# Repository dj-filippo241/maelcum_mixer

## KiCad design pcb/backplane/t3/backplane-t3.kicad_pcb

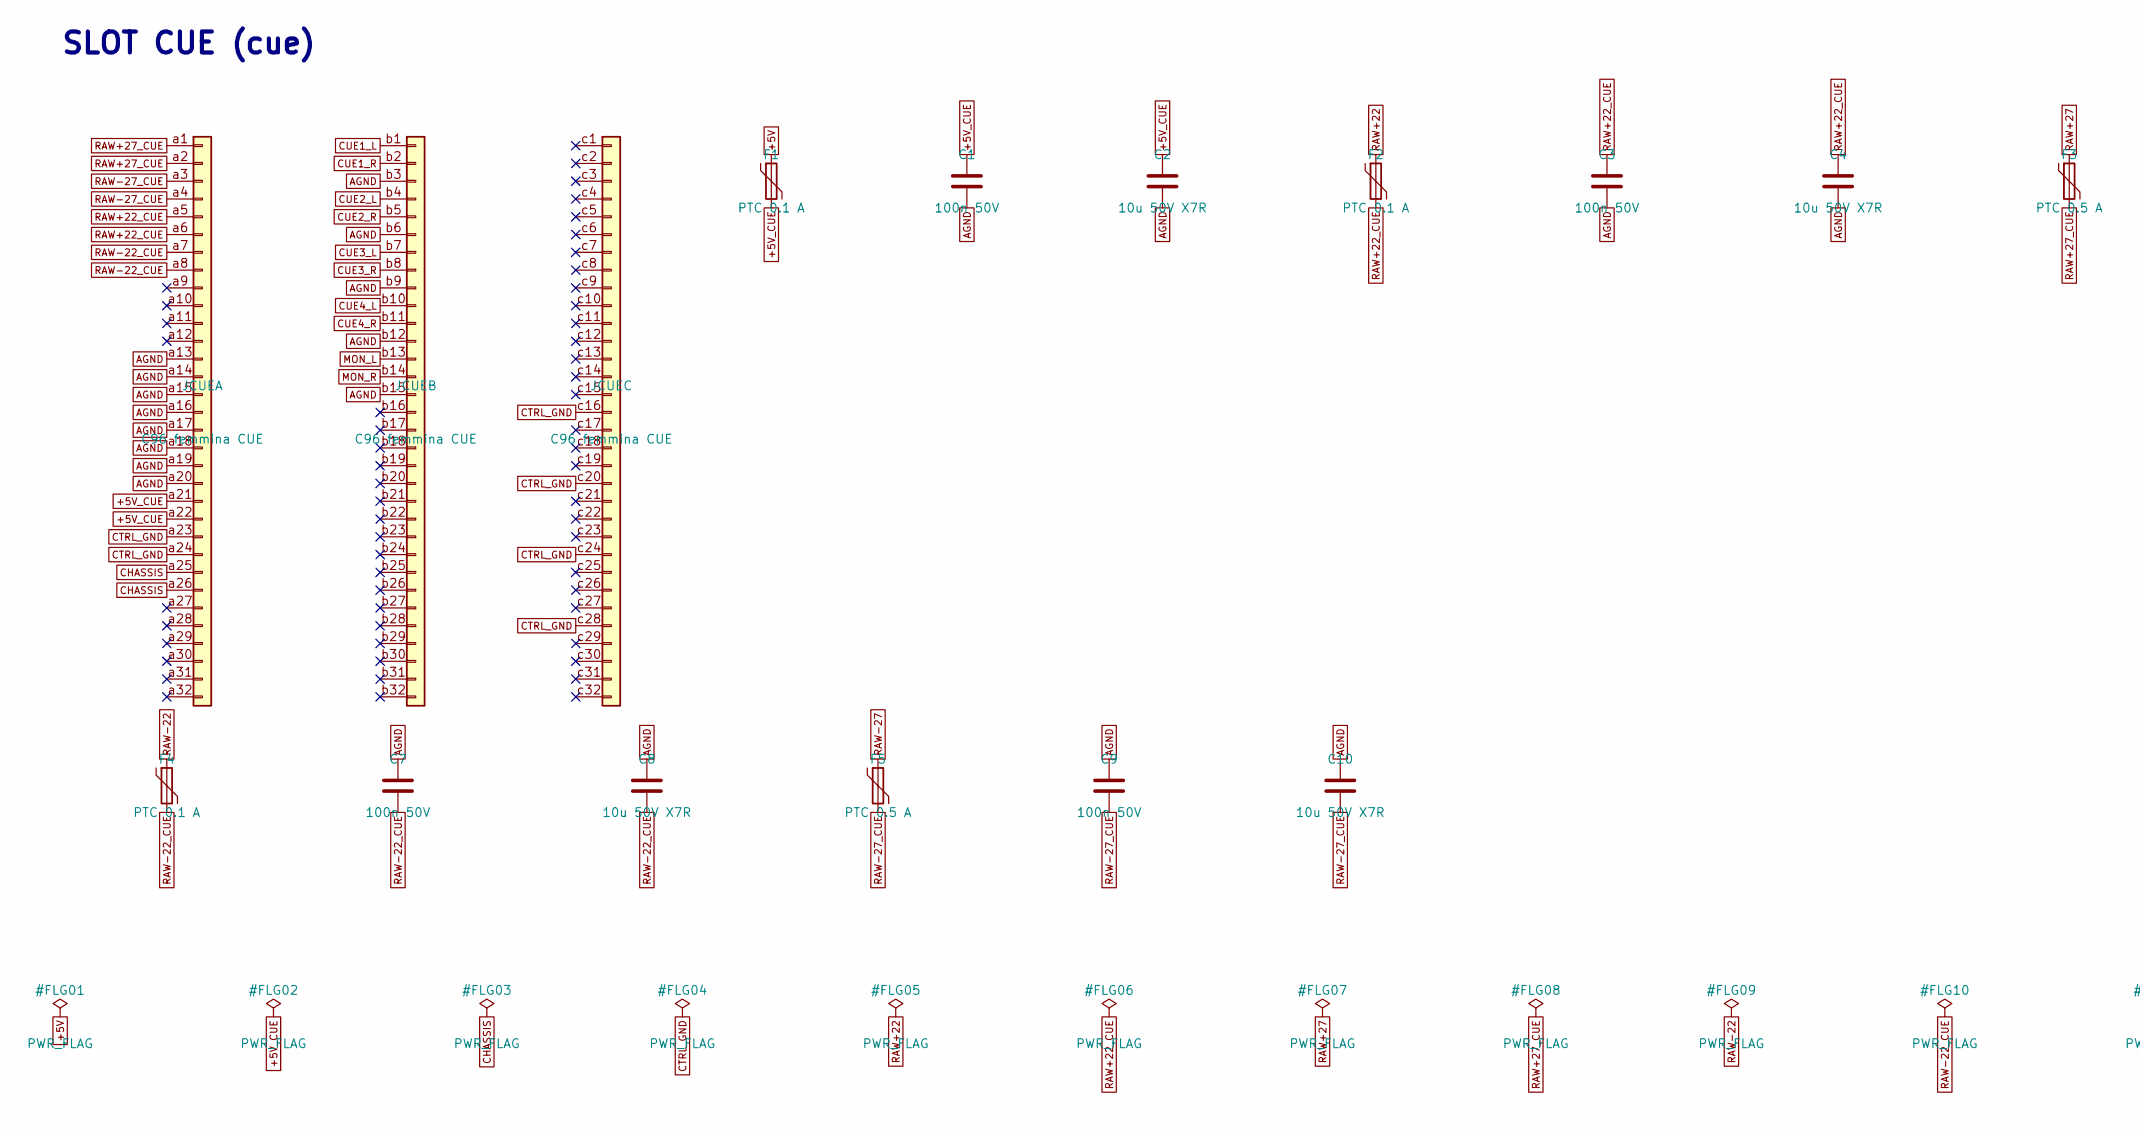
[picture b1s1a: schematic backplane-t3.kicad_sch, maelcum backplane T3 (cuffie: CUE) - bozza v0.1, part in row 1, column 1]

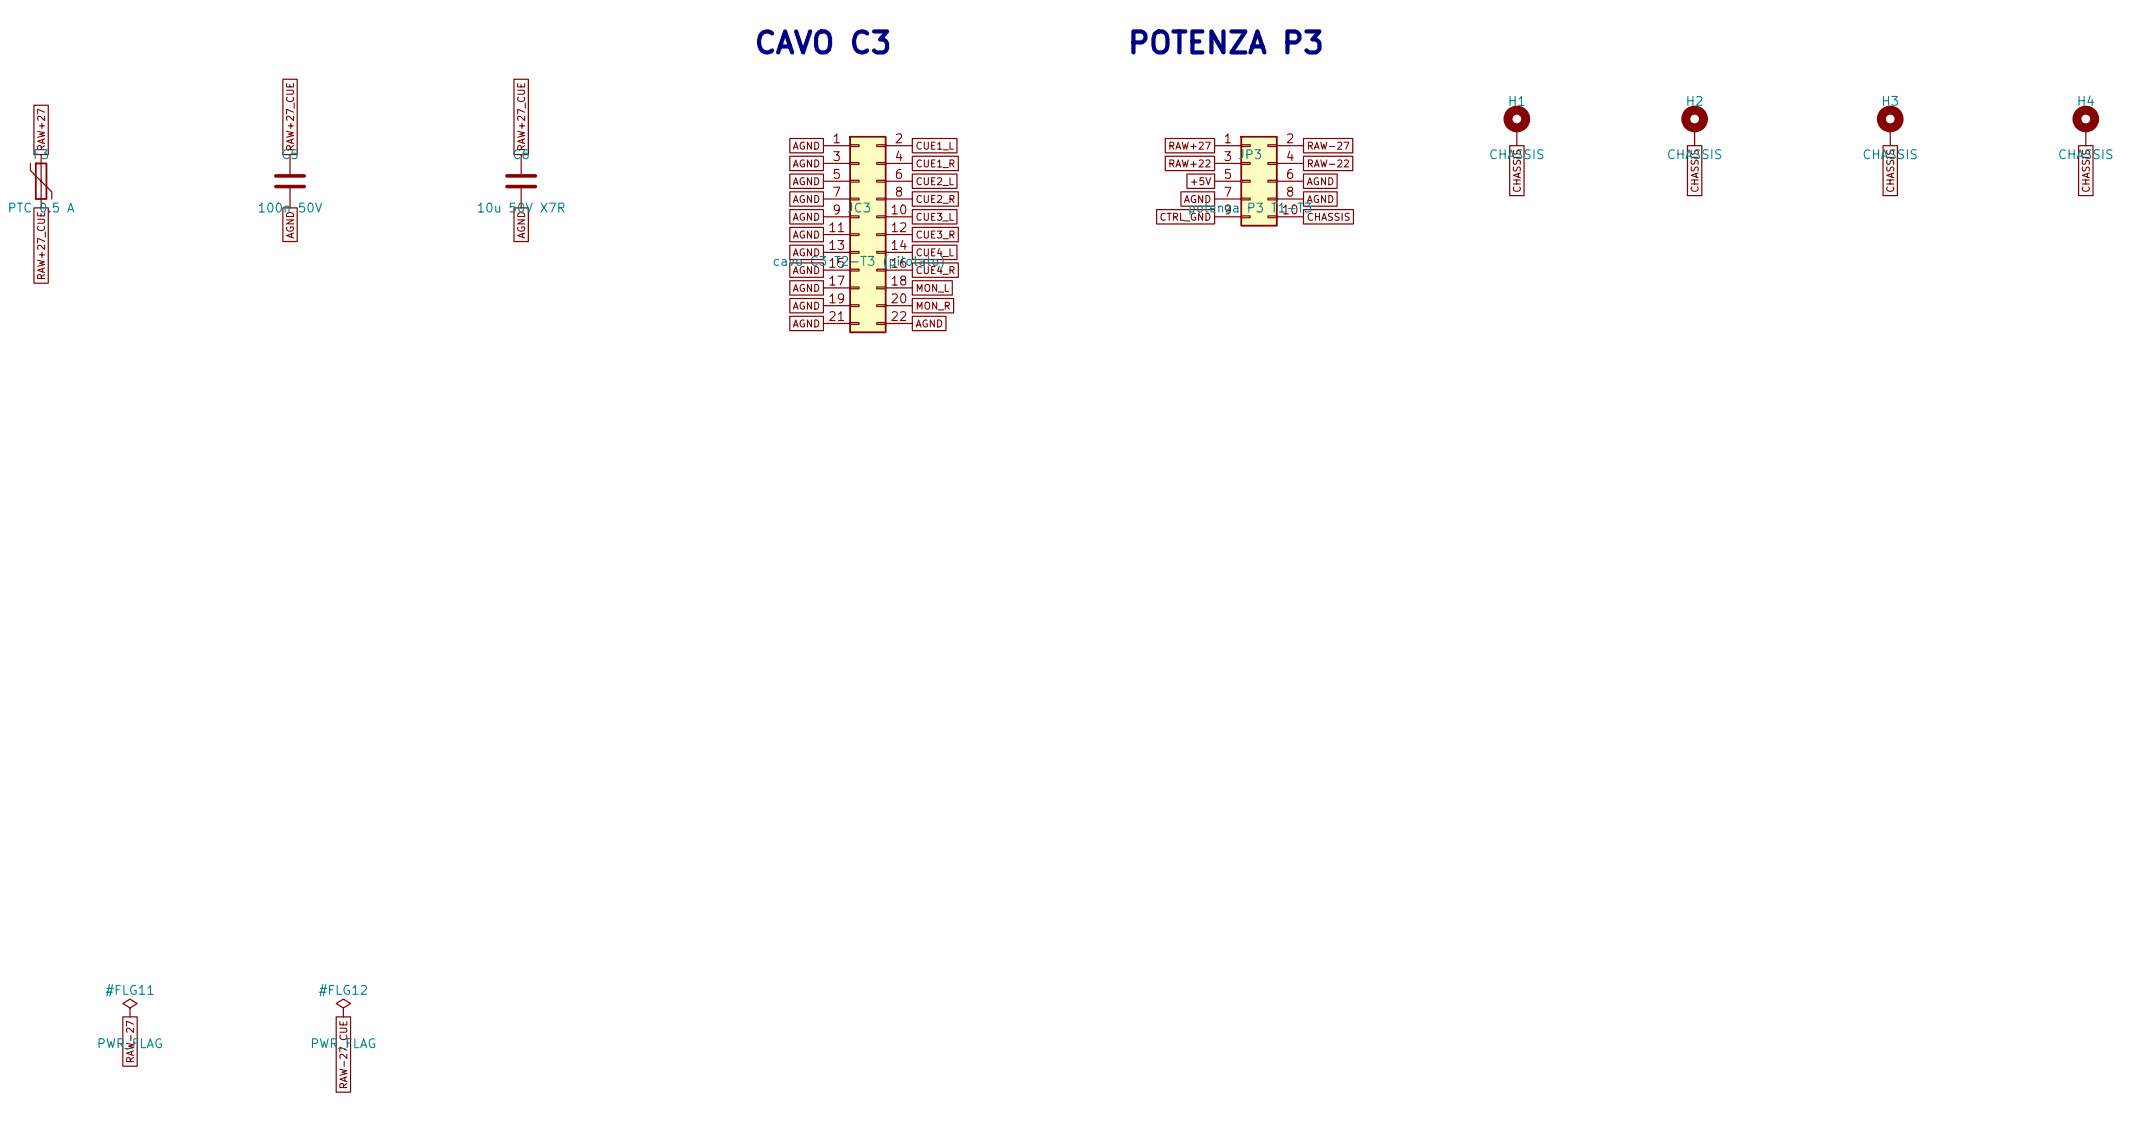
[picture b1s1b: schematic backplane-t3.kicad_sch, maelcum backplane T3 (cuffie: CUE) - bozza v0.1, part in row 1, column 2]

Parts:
C1, C3, C5, C7, C9: 100n 50V; C_0805_2012Metric
C2, C4, C6, C8, C10: 10u 50V X7R; C_1206_3216Metric
F1, F2, F4: PTC 0.1 A; Fuse_1812_4532Metric
F3, F5: PTC 0.5 A; Fuse_1812_4532Metric
H1, H2, H3, H4: CHASSIS; MountingHole_3.2mm_M3_Pad
JC3: cavo C3 T2-T3 (pilotato); IDC-Header_2x11_P2.54mm_Vertical
JCUE: C96 femmina CUE; DIN41612_C_3x32_Female_Vertical_THT
JP3: potenza P3 T1-T3; Molex_Mini-Fit_Jr_5566-10A2_2x05_P4.20mm_Vertical

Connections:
+5V: F1.1, JP3.5
+5V_CUE: C1.1, C2.1, F1.2, JCUE.a21, JCUE.a22
AGND: C1.2, C2.2, C3.2, C4.2, C5.2, C6.2, C7.1, C8.1, C9.1, C10.1, JC3.1, JC3.3, JC3.5, JC3.7, JC3.9, JC3.11, JC3.13, JC3.15, JC3.17, JC3.19, JC3.21, JC3.22, JCUE.a13, JCUE.a14, JCUE.a15, JCUE.a16, JCUE.a17, JCUE.a18, JCUE.a19, JCUE.a20, JCUE.b3, JCUE.b6, JCUE.b9, JCUE.b12, JCUE.b15, JP3.6, JP3.7, JP3.8
CHASSIS: H1.1, H2.1, H3.1, H4.1, JCUE.a25, JCUE.a26, JP3.10
CTRL_GND: JCUE.a23, JCUE.a24, JCUE.c16, JCUE.c20, JCUE.c24, JCUE.c28, JP3.9
CUE1_L: JC3.2, JCUE.b1
CUE1_R: JC3.4, JCUE.b2
CUE2_L: JC3.6, JCUE.b4
CUE2_R: JC3.8, JCUE.b5
CUE3_L: JC3.10, JCUE.b7
CUE3_R: JC3.12, JCUE.b8
CUE4_L: JC3.14, JCUE.b10
CUE4_R: JC3.16, JCUE.b11
MON_L: JC3.18, JCUE.b13
MON_R: JC3.20, JCUE.b14
RAW+22: F2.1, JP3.3
RAW+22_CUE: C3.1, C4.1, F2.2, JCUE.a5, JCUE.a6
RAW+27: F3.1, JP3.1
RAW+27_CUE: C5.1, C6.1, F3.2, JCUE.a1, JCUE.a2
RAW-22: F4.1, JP3.4
RAW-22_CUE: C7.2, C8.2, F4.2, JCUE.a7, JCUE.a8
RAW-27: F5.1, JP3.2
RAW-27_CUE: C9.2, C10.2, F5.2, JCUE.a3, JCUE.a4

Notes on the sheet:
SLOT CUE (cue)
CAVO C3
POTENZA P3

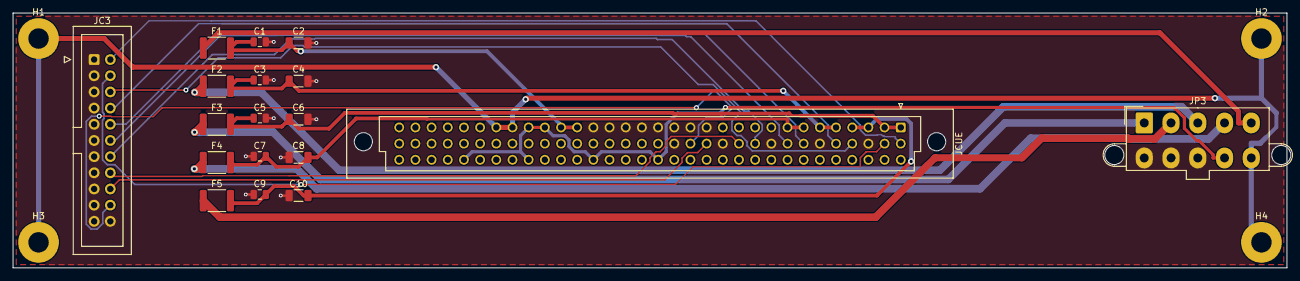
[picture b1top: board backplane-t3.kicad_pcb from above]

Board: 4 copper layers, 200.0 x 40.0 mm, 22 parts (0 on the bottom side), 23 nets.

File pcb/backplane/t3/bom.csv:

quantita;valore;impronta;riferimenti;nota
5;100n 50V;C_0805_2012Metric;C1 C3 C5 C7 C9;bypass di slot (backplane §8)
5;10u 50V X7R;C_1206_3216Metric;C2 C4 C6 C8 C10;bulk di slot (backplane §8); NOTA: MLCC 50 V
3;PTC 0.1 A;Fuse_1812_4532Metric;F1 F2 F4;PTC di slot (psu-esterno §4.3); NOTA: tenuta 0.1 A, >= 33 V, 1812
2;PTC 0.5 A;Fuse_1812_4532Metric;F3 F5;PTC di slot (psu-esterno §4.3); NOTA: tenuta 0.5 A, >= 33 V, 1812
1;cavo C3 T2-T3 (pilotato);IDC-Header_2x11_P2.54mm_Vertical;JC3;NOTA: cavo piatto, ogni segnale fra due fili di massa; solo linee pilotate
1;C96 femmina CUE;DIN41612_C_3x32_Female_Vertical_THT;JCUE;slot CUE, classe cue; pin da pcb/cue (netlist). Fila a a 2.11 mm dal piano medio della scheda di modulo, lato F del modulo verso la fila c (Harting 09 03 196 6921)
1;potenza P3 T1-T3;Molex_Mini-Fit_Jr_5566-10A2_2x05_P4.20mm_Vertical;JP3;NOTA: Mini-Fit Jr 2x5; radiale AGND del tratto fino alla stella del PSU-IN (grounding §2)

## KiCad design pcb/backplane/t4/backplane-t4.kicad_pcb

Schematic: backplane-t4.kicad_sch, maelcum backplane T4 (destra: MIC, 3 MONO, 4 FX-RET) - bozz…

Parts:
C1, C3, C5, C7, C9, C11, C13, C15, C17, C19, C21, C23, C25, C27, C29, C31, C33, C35, C37, C39, C41, C43, C45, C47, C49, C51, C53, C55, C57, C59, C61, C63, C65, C67, C69, C71, C73, C75, C77, C79: 100n 50V; C_0805_2012Metric
C2, C4, C6, C8, C10, C12, C14, C16, C18, C20, C22, C24, C26, C28, C30, C32, C34, C36, C38, C40, C42, C44, C46, C48, C50, C52, C54, C56, C58, C60, C62, C64, C66, C68, C70, C72, C74, C76, C78, C80: 10u 50V X7R; C_1206_3216Metric
F1, F2, F3, F4, F5, F7, F9, F11, F13, F15, F17, F19, F21, F23, F25, F27, F29, F31, F33, F35, F37, F39: PTC 0.1 A; Fuse_1812_4532Metric
F6, F8, F10, F16, F18, F20, F26, F28, F30, F36, F38, F40: PTC 0.2 A; Fuse_1812_4532Metric
F12, F14, F22, F24, F32, F34: PTC 0.05 A; Fuse_1812_4532Metric
H1, H2, H3, H4, H5: CHASSIS; MountingHole_3.2mm_M3_Pad
JC4: cavo C4 T2-T4 (VE); IDC-Header_2x09_P2.54mm_Vertical
JC5: cavo C5 T1-T4 (VE); IDC-Header_2x05_P2.54mm_Vertical
JC6: cavo C6 T1-T4 (pilotato); IDC-Header_2x10_P2.54mm_Vertical
JMIC: C96 femmina MIC; DIN41612_C_3x32_Female_Vertical_THT
JMONO1: C96 femmina MONO1; DIN41612_C_3x32_Female_Vertical_THT
JMONO2: C96 femmina MONO2; DIN41612_C_3x32_Female_Vertical_THT
JMONO3: C96 femmina MONO3; DIN41612_C_3x32_Female_Vertical_THT
JP4: potenza P4 T1-T4; Molex_Mini-Fit_Jr_5566-10A2_2x05_P4.20mm_Vertical
JRET1: C96 femmina RET1; DIN41612_C_3x32_Female_Vertical_THT
JRET2: C96 femmina RET2; DIN41612_C_3x32_Female_Vertical_THT
JRET3: C96 femmina RET3; DIN41612_C_3x32_Female_Vertical_THT
JRET4: C96 femmina RET4; DIN41612_C_3x32_Female_Vertical_THT

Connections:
+5V: F1.1, F6.1, F11.1, F16.1, F21.1, F26.1, F31.1, F36.1, JP4.5
+5V_MIC: C1.1, C2.1, F1.2, JMIC.a21, JMIC.a22
+5V_MONO1: C21.1, C22.1, F11.2, JMONO1.a21, JMONO1.a22
+5V_MONO2: C41.1, C42.1, F21.2, JMONO2.a21, JMONO2.a22
+5V_MONO3: C61.1, C62.1, F31.2, JMONO3.a21, JMONO3.a22
+5V_RET1: C11.1, C12.1, F6.2, JRET1.a21, JRET1.a22
+5V_RET2: C31.1, C32.1, F16.2, JRET2.a21, JRET2.a22
+5V_RET3: C51.1, C52.1, F26.2, JRET3.a21, JRET3.a22
+5V_RET4: C71.1, C72.1, F36.2, JRET4.a21, JRET4.a22
AGND: C1.2, C2.2, C3.2, C4.2, C5.2, C6.2, C7.1, C8.1, C9.1, C10.1, C11.2, C12.2, C13.2, C14.2, C15.2, C16.2, C17.1, C18.1, C19.1, C20.1, C21.2, C22.2, C23.2, C24.2, C25.2, C26.2, C27.1, C28.1, C29.1, C30.1, C31.2, C32.2, C33.2, C34.2, C35.2, C36.2, C37.1, C38.1, C39.1, C40.1, C41.2, C42.2, C43.2, C44.2, C45.2, C46.2, C47.1, C48.1, C49.1, C50.1, C51.2, C52.2, C53.2, C54.2, C55.2, C56.2, C57.1, C58.1, C59.1, C60.1, C61.2, C62.2, C63.2, C64.2, C65.2, C66.2, C67.1, C68.1, C69.1, C70.1, C71.2, C72.2, C73.2, C74.2, C75.2, C76.2, C77.1, C78.1, C79.1, C80.1, JC4.1, JC4.3, JC4.5, JC4.7, JC4.9, JC4.11, JC4.13, JC4.15, JC4.17, JC4.18, JC5.1, JC5.3, JC5.5, JC5.7, JC5.9, JC5.10, JC6.1, JC6.3, JC6.5, JC6.7, JC6.9, JC6.11, JC6.13, JC6.15, JC6.19, JC6.20, JMIC.a13, JMIC.a14, JMIC.a15, JMIC.a16, JMIC.a17, JMIC.a18, JMIC.a19, JMIC.a20, JMIC.b3, JMIC.b6, JMIC.b9, JMIC.b12, JMIC.b15, JMIC.b18, JMIC.b21, JMIC.b24, JMIC.b27, JMIC.b30, JMONO1.a13, JMONO1.a14, JMONO1.a15, JMONO1.a16, JMONO1.a17, JMONO1.a18, JMONO1.a19, JMONO1.a20, JMONO1.b3, JMONO1.b6, JMONO1.b9, JMONO1.b12, JMONO1.b15, JMONO1.b18, JMONO1.b21, JMONO1.b24, JMONO1.b27, JMONO1.b30, JMONO2.a13, JMONO2.a14, JMONO2.a15, JMONO2.a16, JMONO2.a17, JMONO2.a18, JMONO2.a19, JMONO2.a20, JMONO2.b3, JMONO2.b6, JMONO2.b9, JMONO2.b12, JMONO2.b15, JMONO2.b18, JMONO2.b21, JMONO2.b24, JMONO2.b27, JMONO2.b30, JMONO3.a13, JMONO3.a14, JMONO3.a15, JMONO3.a16, JMONO3.a17, JMONO3.a18, JMONO3.a19, JMONO3.a20, JMONO3.b3, JMONO3.b6, JMONO3.b9, JMONO3.b12, JMONO3.b15, JMONO3.b18, JMONO3.b21, JMONO3.b24, JMONO3.b27, JMONO3.b30, JP4.6, JP4.7, JP4.8, JRET1.a13, JRET1.a14, JRET1.a15, JRET1.a16, JRET1.a17, JRET1.a18, JRET1.a19, JRET1.a20, JRET1.b3, JRET1.b6, JRET1.b9, JRET1.b12, JRET1.b15, JRET1.b18, JRET1.b21, JRET1.b24, JRET1.b27, JRET1.b30, JRET2.a13, JRET2.a14, JRET2.a15, JRET2.a16, JRET2.a17, JRET2.a18, JRET2.a19, JRET2.a20, JRET2.b3, JRET2.b6, JRET2.b9, JRET2.b12, JRET2.b15, JRET2.b18, JRET2.b21, JRET2.b24, JRET2.b27, JRET2.b30, JRET3.a13, JRET3.a14, JRET3.a15, JRET3.a16, JRET3.a17, JRET3.a18, JRET3.a19, JRET3.a20, JRET3.b3, JRET3.b6, JRET3.b9, JRET3.b12, JRET3.b15, JRET3.b18, JRET3.b21, JRET3.b24, JRET3.b27, JRET3.b30, JRET4.a13, JRET4.a14, JRET4.a15, JRET4.a16, JRET4.a17, JRET4.a18, JRET4.a19, JRET4.a20, JRET4.b3, JRET4.b6, JRET4.b9, JRET4.b12, JRET4.b15, JRET4.b18, JRET4.b21, JRET4.b24, JRET4.b27, JRET4.b30
CHASSIS: H1.1, H2.1, H3.1, H4.1, H5.1, JMIC.a25, JMIC.a26, JMONO1.a25, JMONO1.a26, JMONO2.a25, JMONO2.a26, JMONO3.a25, JMONO3.a26, JP4.10, JRET1.a25, JRET1.a26, JRET2.a25, JRET2.a26, JRET3.a25, JRET3.a26, JRET4.a25, JRET4.a26
CTRL_GND: JC6.17, JMIC.a23, JMIC.a24, JMIC.c16, JMIC.c20, JMIC.c24, JMIC.c28, JMONO1.a23, JMONO1.a24, JMONO1.c16, JMONO1.c20, JMONO1.c24, JMONO1.c28, JMONO2.a23, JMONO2.a24, JMONO2.c16, JMONO2.c20, JMONO2.c24, JMONO2.c28, JMONO3.a23, JMONO3.a24, JMONO3.c16, JMONO3.c20, JMONO3.c24, JMONO3.c28, JP4.9, JRET1.a23, JRET1.a24, JRET1.c16, JRET1.c20, JRET1.c24, JRET1.c28, JRET2.a23, JRET2.a24, JRET2.c16, JRET2.c20, JRET2.c24, JRET2.c28, JRET3.a23, JRET3.a24, JRET3.c16, JRET3.c20, JRET3.c24, JRET3.c28, JRET4.a23, JRET4.a24, JRET4.c16, JRET4.c20, JRET4.c24, JRET4.c28
GLOBAL_MUTE: JC6.18, JMIC.c9, JMONO1.c9, JMONO2.c9, JMONO3.c9
MSUM2_L: JC6.2, JRET1.b16
MSUM2_R: JC6.4, JRET1.b17
MSUM3_L: JC6.6, JRET2.b16
MSUM3_R: JC6.8, JRET2.b17
MSUM4_L: JC6.10, JRET3.b16
MSUM4_R: JC6.12, JRET3.b17
MSUM5_L: JC6.14, JRET4.b16
MSUM5_R: JC6.16, JRET4.b17
MSUM6_L: JC5.2, JMIC.b1
MSUM6_R: JC5.4, JMIC.b2
MSUM7_L: JC5.6, JMONO1.b1, JMONO2.b1, JMONO3.b1
MSUM7_R: JC5.8, JMONO1.b2, JMONO2.b2, JMONO3.b2
RAW+22: F2.1, F7.1, F12.1, F17.1, F22.1, F27.1, F32.1, F37.1, JP4.3
RAW+22_MIC: C3.1, C4.1, F2.2, JMIC.a5, JMIC.a6
RAW+22_MONO1: C23.1, C24.1, F12.2, JMONO1.a5, JMONO1.a6
RAW+22_MONO2: C43.1, C44.1, F22.2, JMONO2.a5, JMONO2.a6
RAW+22_MONO3: C63.1, C64.1, F32.2, JMONO3.a5, JMONO3.a6
RAW+22_RET1: C13.1, C14.1, F7.2, JRET1.a5, JRET1.a6
RAW+22_RET2: C33.1, C34.1, F17.2, JRET2.a5, JRET2.a6
RAW+22_RET3: C53.1, C54.1, F27.2, JRET3.a5, JRET3.a6
RAW+22_RET4: C73.1, C74.1, F37.2, JRET4.a5, JRET4.a6
RAW+27: F3.1, F8.1, F13.1, F18.1, F23.1, F28.1, F33.1, F38.1, JP4.1
RAW+27_MIC: C5.1, C6.1, F3.2, JMIC.a1, JMIC.a2
RAW+27_MONO1: C25.1, C26.1, F13.2, JMONO1.a1, JMONO1.a2
RAW+27_MONO2: C45.1, C46.1, F23.2, JMONO2.a1, JMONO2.a2
RAW+27_MONO3: C65.1, C66.1, F33.2, JMONO3.a1, JMONO3.a2
RAW+27_RET1: C15.1, C16.1, F8.2, JRET1.a1, JRET1.a2
RAW+27_RET2: C35.1, C36.1, F18.2, JRET2.a1, JRET2.a2
RAW+27_RET3: C55.1, C56.1, F28.2, JRET3.a1, JRET3.a2
RAW+27_RET4: C75.1, C76.1, F38.2, JRET4.a1, JRET4.a2
RAW-22: F4.1, F9.1, F14.1, F19.1, F24.1, F29.1, F34.1, F39.1, JP4.4
RAW-22_MIC: C7.2, C8.2, F4.2, JMIC.a7, JMIC.a8
RAW-22_MONO1: C27.2, C28.2, F14.2, JMONO1.a7, JMONO1.a8
RAW-22_MONO2: C47.2, C48.2, F24.2, JMONO2.a7, JMONO2.a8
RAW-22_MONO3: C67.2, C68.2, F34.2, JMONO3.a7, JMONO3.a8
RAW-22_RET1: C17.2, C18.2, F9.2, JRET1.a7, JRET1.a8
RAW-22_RET2: C37.2, C38.2, F19.2, JRET2.a7, JRET2.a8
RAW-22_RET3: C57.2, C58.2, F29.2, JRET3.a7, JRET3.a8
RAW-22_RET4: C77.2, C78.2, F39.2, JRET4.a7, JRET4.a8
RAW-27: F5.1, F10.1, F15.1, F20.1, F25.1, F30.1, F35.1, F40.1, JP4.2
RAW-27_MIC: C9.2, C10.2, F5.2, JMIC.a3, JMIC.a4
RAW-27_MONO1: C29.2, C30.2, F15.2, JMONO1.a3, JMONO1.a4
RAW-27_MONO2: C49.2, C50.2, F25.2, JMONO2.a3, JMONO2.a4
RAW-27_MONO3: C69.2, C70.2, F35.2, JMONO3.a3, JMONO3.a4
RAW-27_RET1: C19.2, C20.2, F10.2, JRET1.a3, JRET1.a4
RAW-27_RET2: C39.2, C40.2, F20.2, JRET2.a3, JRET2.a4
RAW-27_RET3: C59.2, C60.2, F30.2, JRET3.a3, JRET3.a4
RAW-27_RET4: C79.2, C80.2, F40.2, JRET4.a3, JRET4.a4
S1_L: JC4.2, JMIC.b4, JMONO1.b4, JMONO2.b4, JMONO3.b4, JRET1.b1, JRET1.b4, JRET2.b4, JRET3.b4, JRET4.b4
S1_R: JC4.4, JMIC.b5, JMONO1.b5, JMONO2.b5, JMONO3.b5, JRET1.b2, JRET1.b5, JRET2.b5, JRET3.b5, JRET4.b5
S2_L: JC4.6, JMIC.b7, JMONO1.b7, JMONO2.b7, JMONO3.b7, JRET1.b7, JRET2.b1, JRET2.b7, JRET3.b7, JRET4.b7
S2_R: JC4.8, JMIC.b8, JMONO1.b8, JMONO2.b8, JMONO3.b8, JRET1.b8, JRET2.b2, JRET2.b8, JRET3.b8, JRET4.b8
S3_L: JC4.10, JMIC.b10, JMONO1.b10, JMONO2.b10, JMONO3.b10, JRET1.b10, JRET2.b10, JRET3.b1, JRET3.b10, JRET4.b10
S3_R: JC4.12, JMIC.b11, JMONO1.b11, JMONO2.b11, JMONO3.b11, JRET1.b11, JRET2.b11, JRET3.b2, JRET3.b11, JRET4.b11
S4_L: JC4.14, JMIC.b13, JMONO1.b13, JMONO2.b13, JMONO3.b13, JRET1.b13, JRET2.b13, JRET3.b13, JRET4.b1, JRET4.b13
S4_R: JC4.16, JMIC.b14, JMONO1.b14, JMONO2.b14, JMONO3.b14, JRET1.b14, JRET2.b14, JRET3.b14, JRET4.b2, JRET4.b14

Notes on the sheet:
SLOT MIC (mic)
SLOT RET1 (fx-ret)
SLOT MONO1 (mono)
SLOT RET2 (fx-ret)
SLOT MONO2 (mono)
SLOT RET3 (fx-ret)
SLOT MONO3 (mono)
SLOT RET4 (fx-ret)
CAVO C4
CAVO C5
CAVO C6
POTENZA P4

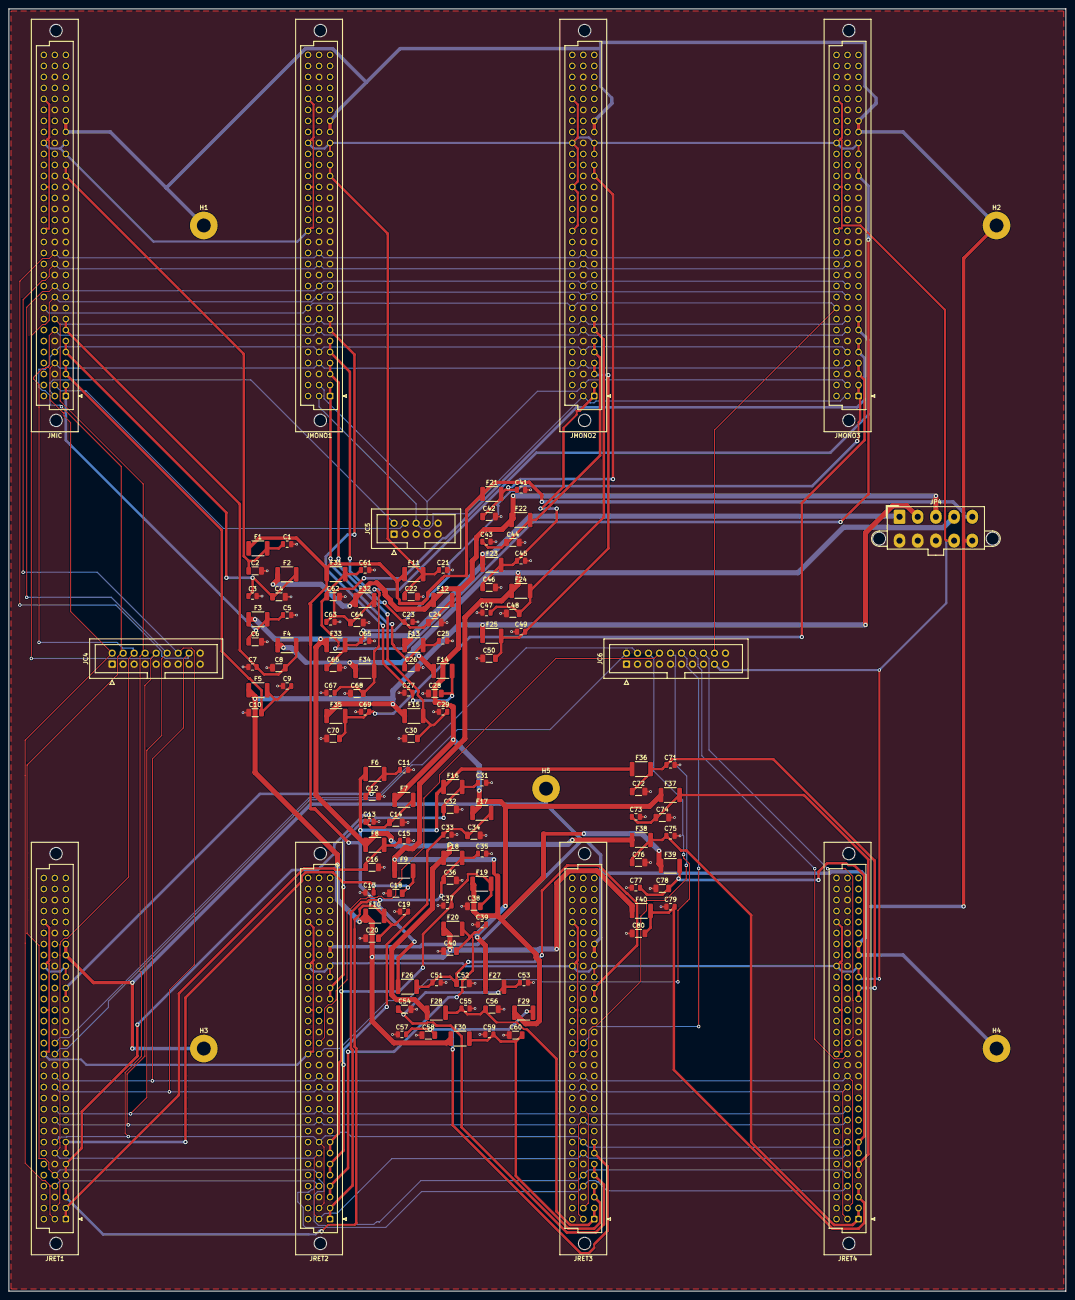
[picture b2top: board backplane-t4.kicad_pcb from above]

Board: 4 copper layers, 244.0 x 296.0 mm, 137 parts (0 on the bottom side), 69 nets.

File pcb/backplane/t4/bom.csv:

quantita;valore;impronta;riferimenti;nota
40;100n 50V;C_0805_2012Metric;C1 C3 C5 C7 C9 C11 C13 C15 C17 C19 C21 C23 C25 C27 C29 C31 C33 C35 C37 C39 C41 C43 C45 C47 C49 C51 C53 C55 C57 C59 C61 C63 C65 C67 C69 C71 C73 C75 C77 C79;bypass di slot (backplane §8)
40;10u 50V X7R;C_1206_3216Metric;C2 C4 C6 C8 C10 C12 C14 C16 C18 C20 C22 C24 C26 C28 C30 C32 C34 C36 C38 C40 C42 C44 C46 C48 C50 C52 C54 C56 C58 C60 C62 C64 C66 C68 C70 C72 C74 C76 C78 C80;bulk di slot (backplane §8); NOTA: MLCC 50 V
22;PTC 0.1 A;Fuse_1812_4532Metric;F1 F2 F3 F4 F5 F7 F9 F11 F13 F15 F17 F19 F21 F23 F25 F27 F29 F31 F33 F35 F37 F39;PTC di slot (psu-esterno §4.3); NOTA: tenuta 0.1 A, >= 33 V, 1812
6;PTC 0.05 A;Fuse_1812_4532Metric;F12 F14 F22 F24 F32 F34;PTC di slot (psu-esterno §4.3); NOTA: tenuta 0.05 A, >= 33 V, 1812
12;PTC 0.2 A;Fuse_1812_4532Metric;F6 F8 F10 F16 F18 F20 F26 F28 F30 F36 F38 F40;PTC di slot (psu-esterno §4.3); NOTA: tenuta 0.2 A, >= 33 V, 1812
1;cavo C4 T2-T4 (VE);IDC-Header_2x09_P2.54mm_Vertical;JC4;NOTA: cavo piatto, ogni segnale fra due fili di massa; solo net a massa virtuale
1;cavo C5 T1-T4 (VE);IDC-Header_2x05_P2.54mm_Vertical;JC5;NOTA: cavo piatto, ogni segnale fra due fili di massa; solo net a massa virtuale
1;cavo C6 T1-T4 (pilotato);IDC-Header_2x10_P2.54mm_Vertical;JC6;NOTA: cavo piatto, ogni segnale fra due fili di massa; solo linee pilotate
1;C96 femmina MIC;DIN41612_C_3x32_Female_Vertical_THT;JMIC;slot MIC, classe mic; pin da pcb/mic (netlist). Fila a a 2.11 mm dal piano medio della scheda di modulo, lato F del modulo verso la fila c (Harting 09 03 196 6921)
1;C96 femmina MONO1;DIN41612_C_3x32_Female_Vertical_THT;JMONO1;slot MONO1, classe mono; pin da pcb/mono (netlist). Fila a a 2.11 mm dal piano medio della scheda di modulo, lato F del modulo verso la fila c (Harting 09 03 196 6921)
1;C96 femmina MONO2;DIN41612_C_3x32_Female_Vertical_THT;JMONO2;slot MONO2, classe mono; pin da pcb/mono (netlist). Fila a a 2.11 mm dal piano medio della scheda di modulo, lato F del modulo verso la fila c (Harting 09 03 196 6921)
1;C96 femmina MONO3;DIN41612_C_3x32_Female_Vertical_THT;JMONO3;slot MONO3, classe mono; pin da pcb/mono (netlist). Fila a a 2.11 mm dal piano medio della scheda di modulo, lato F del modulo verso la fila c (Harting 09 03 196 6921)
1;potenza P4 T1-T4;Molex_Mini-Fit_Jr_5566-10A2_2x05_P4.20mm_Vertical;JP4;NOTA: Mini-Fit Jr 2x5; radiale AGND del tratto fino alla stella del PSU-IN (grounding §2)
1;C96 femmina RET1;DIN41612_C_3x32_Female_Vertical_THT;JRET1;slot RET1, classe fx-ret; pin da pcb/fx-ret (netlist). Fila a a 2.11 mm dal piano medio della scheda di modulo, lato F del modulo verso la fila c (Harting 09 03 196 6921)
1;C96 femmina RET2;DIN41612_C_3x32_Female_Vertical_THT;JRET2;slot RET2, classe fx-ret; pin da pcb/fx-ret (netlist). Fila a a 2.11 mm dal piano medio della scheda di modulo, lato F del modulo verso la fila c (Harting 09 03 196 6921)
1;C96 femmina RET3;DIN41612_C_3x32_Female_Vertical_THT;JRET3;slot RET3, classe fx-ret; pin da pcb/fx-ret (netlist). Fila a a 2.11 mm dal piano medio della scheda di modulo, lato F del modulo verso la fila c (Harting 09 03 196 6921)
1;C96 femmina RET4;DIN41612_C_3x32_Female_Vertical_THT;JRET4;slot RET4, classe fx-ret; pin da pcb/fx-ret (netlist). Fila a a 2.11 mm dal piano medio della scheda di modulo, lato F del modulo verso la fila c (Harting 09 03 196 6921)

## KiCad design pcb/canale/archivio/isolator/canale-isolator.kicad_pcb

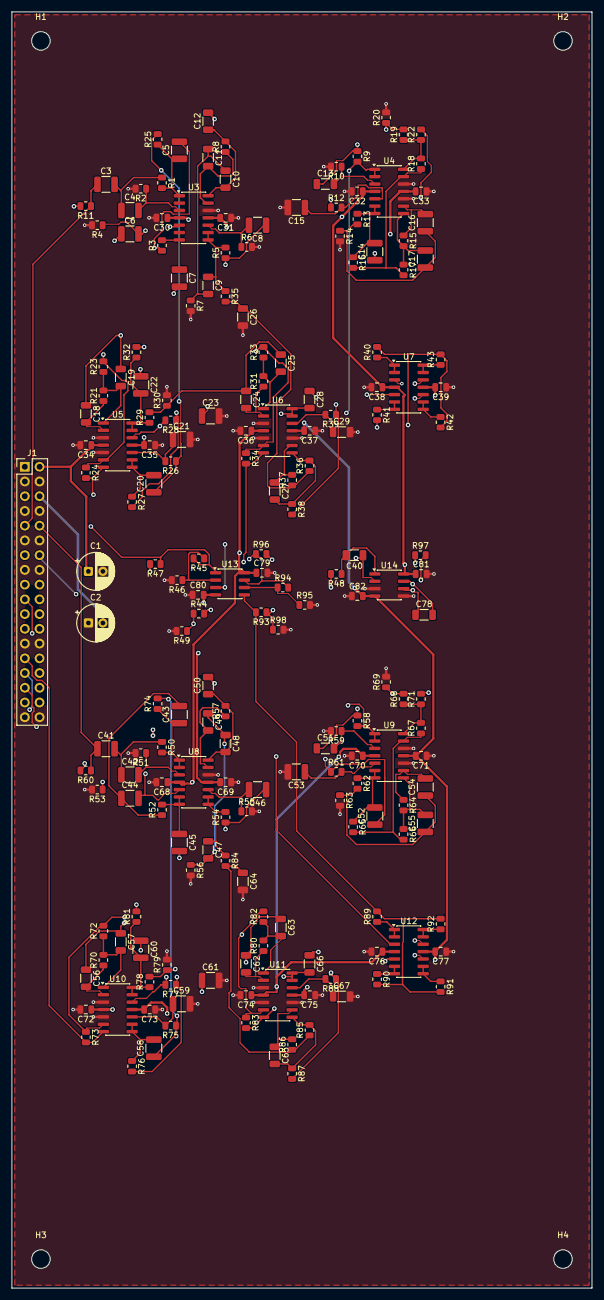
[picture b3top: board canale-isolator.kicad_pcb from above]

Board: 4 copper layers, 100.0 x 220.0 mm, 197 parts (0 on the bottom side), 123 nets.

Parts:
C1, C2: 47u 25V; CP_Radial_D6.3mm_P2.50mm
C3, C4, C14, C15, C41, C42, C52, C53: 220n C0G; C_1210_3225Metric
C5, C6, C7, C8, C21, C23, C43, C44, C45, C46, C59, C61: 100n C0G; C_1210_3225Metric
C9, C10, C11, C12, C13, C29, C47, C48, C49, C50, C51, C67: 10n C0G; C_1206_3216Metric
C16, C54: 94n C0G; C_1210_3225Metric
C17, C55: 47n C0G; C_1210_3225Metric
C18, C24, C56, C62: 9n4 C0G; C_1206_3216Metric
C19, C25, C27, C57, C63, C65: 4n7 C0G; C_1206_3216Metric
C20, C22, C58, C60: 200n C0G; C_1210_3225Metric
C26, C64: 21n15 C0G; C_1206_3216Metric
C28, C66: 20n C0G; C_1206_3216Metric
C30, C31, C32, C33, C34, C35, C36, C37, C38, C39, C68, C69, C70, C71, C72, C73, C74, C75, C76, C77, C79, C80, C81, C82: 100n; C_0805_2012Metric
C40, C78: 27n C0G; C_1206_3216Metric
H1, H2, H3, H4: M3; MountingHole_3.2mm_M3
J1: 2x18 ponte isolator; PinHeader_2x18_P2.54mm_Vertical
R1, R2, R11, R12, R50, R51, R60, R61: 4k81 0.1%; R_0805_2012Metric
R3, R5, R25, R26, R27, R28, R52, R54, R74, R75, R76, R77: 3k20 0.1%; R_0805_2012Metric
R4, R6, R53, R55: 6k42 0.1%; R_0805_2012Metric
R7, R56: 2k37 0.1%; R_0805_2012Metric
R8, R57: 10k7 0.1%; R_0805_2012Metric
R9, R38, R39, R58, R87, R88: 3k57 0.1%; R_0805_2012Metric
R10, R59: 7k15 0.1%; R_0805_2012Metric
R13, R62: 6k81 0.1%; R_0805_2012Metric
R14, R63: 13k7 0.1%; R_0805_2012Metric
R15, R64: 10k2 0.1%; R_0805_2012Metric
R16, R18, R22, R24, R32, R34, R65, R67, R71, R73, R81, R83: 10k 0.1%; R_0805_2012Metric
R17, R23, R33, R66, R72, R82: 4k99 0.1%; R_0805_2012Metric
R19, R29, R68, R78: 7k59 0.1%; R_0805_2012Metric
R20, R30, R69, R79: 15k2 0.1%; R_0805_2012Metric
R21, R31, R70, R80: 11k4 0.1%; R_0805_2012Metric
R35, R36, R37, R84, R85, R86: 5k05 0.1%; R_0805_2012Metric
R40, R41, R42, R43, R89, R90, R91, R92: 2k49 0.1%; R_0805_2012Metric
R44, R93: 2k 0.1%; R_0805_2012Metric
R45, R94: 1k8 0.1%; R_0805_2012Metric
R46, R95: 200 0.1%; R_0805_2012Metric
R47, R96: 1M; R_0805_2012Metric
R48, R97: 100k; R_0805_2012Metric
R49, R98: 499 0.1%; R_0805_2012Metric
U3, U4, U5, U6, U7, U8, U9, U10, U11, U12: OPA1654AIDR; SOIC-14_3.9x8.7mm_P1.27mm
U13: OPA1612AIDR; SOIC-8_3.9x4.9mm_P1.27mm
U14: OPA1642AIDR; SOIC-8_3.9x4.9mm_P1.27mm

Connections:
+18V: C1.1, C30.1, C32.1, C34.1, C36.1, C38.1, C68.1, C70.1, C72.1, C74.1, C76.1, C79.1, C81.1, J1.1, J1.2, U3.4, U4.4, U5.4, U6.4, U7.4, U8.4, U9.4, U10.4, U11.4, U12.4, U13.8, U14.8
-18V: C2.2, C31.2, C33.2, C35.2, C37.2, C39.2, C69.2, C71.2, C73.2, C75.2, C77.2, C80.2, C82.2, J1.5, J1.6, U3.11, U4.11, U5.11, U6.11, U7.11, U8.11, U9.11, U10.11, U11.11, U12.11, U13.4, U14.4
AGND: C1.2, C2.1, C15.2, C21.2, C23.2, C26.2, C29.2, C30.2, C31.1, C32.2, C33.1, C34.2, C35.1, C36.2, C37.1, C38.2, C39.1, C53.2, C59.2, C61.2, C64.2, C67.2, C68.2, C69.1, C70.2, C71.1, C72.2, C73.1, C74.2, C75.1, C76.2, C77.1, C79.2, C80.1, C81.2, C82.1, J1.3, J1.4, J1.7, J1.8, J1.11, J1.12, J1.15, J1.16, J1.25, J1.26, J1.35, J1.36, R2.2, R4.2, R6.2, R7.2, R10.2, R14.2, R20.2, R30.2, R46.2, R49.2, R51.2, R53.2, R55.2, R56.2, R59.2, R63.2, R69.2, R79.2, R95.2, R98.2, U3.12, U4.10, U4.12, U5.3, U5.5, U6.3, U6.5, U6.10, U8.12, U9.10, U9.12, U10.3, U10.5, U11.3, U11.5, U11.10, U14.3, U14.5
APBP1_L: C17.2, R15.2, R17.1, U4.8
APBP1_R: C55.2, R64.2, R66.1, U9.8
APBP2_L: C19.2, R21.2, R23.1, U5.1
APBP2_R: C57.2, R70.2, R72.1, U10.1
APBP3_L: C25.2, R31.2, R33.1, U6.1
APBP3_R: C63.2, R80.2, R82.1, U11.1
APMP1_L: C16.2, R15.1, U4.9
APMP1_R: C54.2, R64.1, U9.9
APMP2_L: C18.2, R21.1, U5.2
APMP2_R: C56.2, R70.1, U10.2
APMP3_L: C24.2, R31.1, U6.2
APMP3_R: C62.2, R80.1, U11.2
APNP1_L: C16.1, C17.1, R13.2, R14.1
APNP1_R: C54.1, C55.1, R62.2, R63.1
APNP2_L: C18.1, C19.1, R19.2, R20.1
APNP2_R: C56.1, C57.1, R68.2, R69.1
APNP3_L: C24.1, C25.1, R29.2, R30.1
APNP3_R: C62.1, C63.1, R78.2, R79.1
APSP1_L: R16.2, R17.2, R18.1, U4.13
APSP1_R: R65.2, R66.2, R67.1, U9.13
APSP2_L: R22.2, R23.2, R24.1, U5.6
APSP2_R: R71.2, R72.2, R73.1, U10.6
APSP3_L: R32.2, R33.2, R34.1, U6.6
APSP3_R: R81.2, R82.2, R83.1, U11.6
EQ_L: J1.13, R45.2, R47.1, U13.1
EQ_R: J1.14, R94.2, R96.1, U13.7
GO_L: C3.1, J1.9, R11.1
GO_R: C41.1, J1.10, R60.1
HA_L: C27.2, R36.2, R38.1, U6.8
HA_R: C65.2, R85.2, R87.1, U11.8
HIO_L: J1.23, R9.2, U4.1, U4.2
HIO_R: J1.33, R58.2, U9.1, U9.2
K1W_L: J1.18, U7.3
K1W_R: J1.28, U12.3
K1_L: R40.1, U7.1, U7.2
K1_R: R89.1, U12.1, U12.2
K2W_L: J1.20, U7.5
K2W_R: J1.30, U12.5
K2_L: R41.1, U7.6, U7.7
K2_R: R90.1, U12.6, U12.7
K3W_L: J1.22, U7.10
K3W_R: J1.32, U12.10
K3_L: R42.1, U7.8, U7.9
K3_R: R91.1, U12.8, U12.9
K4W_L: J1.24, U7.12
K4W_R: J1.34, U12.12
K4_L: R43.1, U7.13, U7.14
K4_R: R92.1, U12.13, U12.14
LA_L: C14.2, R13.1, R16.1, U4.6, U4.7
LA_R: C52.2, R62.1, R65.1, U9.6, U9.7
LB_L: R18.2, R19.1, R22.1, U4.14
LB_R: R67.2, R68.1, R71.1, U9.14
LMO_L: J1.19, R34.2, U6.7
LMO_R: J1.29, R83.2, U11.7
LOO_L: J1.17, R24.2, U5.7
LOO_R: J1.27, R73.2, U10.7
MA_L: C20.2, R27.1, U5.8, U5.9
MA_R: C58.2, R76.1, U10.8, U10.9
MB_L: C22.2, R29.1, R32.1, U5.13, U5.14
MB_R: C60.2, R78.1, R81.1, U10.13, U10.14
MCN_L: C27.1, R37.2, U6.9
MCN_R: C65.1, R86.2, U11.9
MCX_L: C26.1, R35.2, R36.1, R37.1
MCX_R: C64.1, R84.2, R85.1, R86.1
MHN_L: C11.2, R8.1, U3.13
MHN_R: C49.2, R57.1, U8.13
MHO_L: C28.2, J1.21, U6.13, U6.14
MHO_R: C66.2, J1.31, U11.13, U11.14
MHX_L: C9.2, C10.1, C11.1, R7.1
MHX_R: C47.2, C48.1, C49.1, R56.1
NGS_L: R45.1, R46.1, U13.2
NGS_R: R94.1, R95.1, U13.6
R1_L: C5.1, R1.2, R25.1, U3.1, U3.2
R1_R: C43.1, R50.2, R74.1, U8.1, U8.2
R2A_L: C7.1, R3.2, U3.6, U3.7
R2A_R: C45.1, R52.2, U8.6, U8.7
R2_L: C9.1, R5.2, R35.1, U3.8, U3.9
R2_R: C47.1, R54.2, R84.1, U8.8, U8.9
R3A_L: C10.2, C12.1, R8.2, U3.14
R3A_R: C48.2, C50.1, R57.2, U8.14
SKAA1_L: C14.1, R11.2, R12.1
SKAA1_R: C52.1, R60.2, R61.1
SKAB1_L: C20.1, R25.2, R26.1
SKAB1_R: C58.1, R74.2, R75.1
SKAB2_L: C22.1, R27.2, R28.1
SKAB2_R: C60.1, R76.2, R77.1
SKAC2_L: C28.1, R38.2, R39.1
SKAC2_R: C66.1, R87.2, R88.1
SKAG2_L: C7.2, C8.1, R5.1
SKAG2_R: C45.2, C46.1, R54.1
SKAH1_L: C3.2, C4.1, R1.1
SKAH1_R: C41.2, C42.1, R50.1
SKAH2_L: C5.2, C6.1, R3.1
SKAH2_R: C43.2, C44.1, R52.1
SKAH3B_L: C12.2, C13.1, R9.1
SKAH3B_R: C50.2, C51.1, R58.1
SKBA1_L: C15.1, R12.2, U4.5
SKBA1_R: C53.1, R61.2, U9.5
SKBB1_L: C21.1, R26.2, U5.10
SKBB1_R: C59.1, R75.2, U10.10
SKBB2_L: C23.1, R28.2, U5.12
SKBB2_R: C61.1, R77.2, U10.12
SKBC2_L: C29.1, R39.2, U6.12
SKBC2_R: C67.1, R88.2, U11.12
SKBG2_L: C8.2, R6.1, U3.10
SKBG2_R: C46.2, R55.1, U8.10
SKBH1_L: C4.2, R2.1, U3.3
SKBH1_R: C42.2, R51.1, U8.3
SKBH2_L: C6.2, R4.1, U3.5
SKBH2_R: C44.2, R53.1, U8.5
SKBH3B_L: C13.2, R10.1, U4.3
SKBH3B_R: C51.2, R59.1, U9.3
SP_L: R40.2, R41.2, R42.2, R43.2, R44.2, U13.3
SP_R: R89.2, R90.2, R91.2, R92.2, R93.2, U13.5
SVI_L: C40.1, R47.2, U14.2
SVI_R: C78.1, R96.2, U14.6
SVO_L: C40.2, R48.1, U14.1
SVO_R: C78.2, R97.1, U14.7
SV_L: R44.1, R48.2, R49.1
SV_R: R93.1, R97.2, R98.1

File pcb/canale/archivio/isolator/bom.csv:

quantita;valore;impronta;riferimenti;nota
2;47u 25V;CP_Radial_D6.3mm_P2.50mm;C1 C2;NOTA: bulk locale dopo il cavo
2;94n C0G;C_1210_3225Metric;C16 C54;NOTA: 2C, coppia in parallelo da fissare col layout (RISULTATI-incroci-C §1)
2;47n C0G;C_1210_3225Metric;C17 C55;
4;9n4 C0G;C_1206_3216Metric;C18 C24 C56 C62;NOTA: 2C, coppia in parallelo da fissare col layout (RISULTATI-incroci-C §1)
6;4n7 C0G;C_1206_3216Metric;C19 C25 C27 C57 C63 C65;
4;200n C0G;C_1210_3225Metric;C20 C22 C58 C60;NOTA: coppia in parallelo da fissare col layout
2;21n15 C0G;C_1206_3216Metric;C26 C64;NOTA: 4,5 x 4,7n, coppia in parallelo da fissare col layout
2;20n C0G;C_1206_3216Metric;C28 C66;NOTA: coppia in parallelo da fissare col layout
8;220n C0G;C_1210_3225Metric;C3 C4 C14 C15 C41 C42 C52 C53;
24;100n;C_0805_2012Metric;C30 C31 C32 C33 C34 C35 C36 C37 C38 C39 C68 C69 C70 C71 C72 C73 C74 C75 C76 C77 C79 C80 C81 C82;
2;27n C0G;C_1206_3216Metric;C40 C78;integratore 1M/27n
12;100n C0G;C_1210_3225Metric;C5 C6 C7 C8 C21 C23 C43 C44 C45 C46 C59 C61;
12;10n C0G;C_1206_3216Metric;C9 C10 C11 C12 C13 C29 C47 C48 C49 C50 C51 C67;
1;2x18 ponte isolator;PinHeader_2x18_P2.54mm_Vertical;J1;NOTA: cavo piatto 2x18 dalla scheda segnale (J4 di canale.py)
8;4k81 0.1%;R_0805_2012Metric;R1 R2 R11 R12 R50 R51 R60 R61;
2;7k15 0.1%;R_0805_2012Metric;R10 R59;
2;6k81 0.1%;R_0805_2012Metric;R13 R62;
2;13k7 0.1%;R_0805_2012Metric;R14 R63;
2;10k2 0.1%;R_0805_2012Metric;R15 R64;
12;10k 0.1%;R_0805_2012Metric;R16 R18 R22 R24 R32 R34 R65 R67 R71 R73 R81 R83;
6;4k99 0.1%;R_0805_2012Metric;R17 R23 R33 R66 R72 R82;sim 5k: E96 4,99k
4;7k59 0.1%;R_0805_2012Metric;R19 R29 R68 R78;
4;15k2 0.1%;R_0805_2012Metric;R20 R30 R69 R79;
4;11k4 0.1%;R_0805_2012Metric;R21 R31 R70 R80;
12;3k20 0.1%;R_0805_2012Metric;R3 R5 R25 R26 R27 R28 R52 R54 R74 R75 R76 R77;
2;5k05 0.1%;R_0805_2012Metric;R35 R84;calcolo 5,07k
4;5k05 0.1%;R_0805_2012Metric;R36 R37 R85 R86;
4;6k42 0.1%;R_0805_2012Metric;R4 R6 R53 R55;
8;2k49 0.1%;R_0805_2012Metric;R40 R41 R42 R43 R89 R90 R91 R92;
2;2k 0.1%;R_0805_2012Metric;R44 R93;ramo del servo
2;1k8 0.1%;R_0805_2012Metric;R45 R94;
2;200 0.1%;R_0805_2012Metric;R46 R95;
2;1M;R_0805_2012Metric;R47 R96;
2;100k;R_0805_2012Metric;R48 R97;
2;499 0.1%;R_0805_2012Metric;R49 R98;polo 0,058 Hz, corsa +-129 mV
2;2k37 0.1%;R_0805_2012Metric;R7 R56;calcolo 2,38k
2;10k7 0.1%;R_0805_2012Metric;R8 R57;
6;3k57 0.1%;R_0805_2012Metric;R9 R38 R39 R58 R87 R88;
1;OPA1654AIDR;SOIC-14_3.9x8.7mm_P1.27mm;U10;isolator lato R, sezioni 9-12
1;OPA1654AIDR;SOIC-14_3.9x8.7mm_P1.27mm;U11;isolator lato R, sezioni 13-16
1;OPA1654AIDR;SOIC-14_3.9x8.7mm_P1.27mm;U12;isolator lato R, sezioni 17-20
1;OPA1612AIDR;SOIC-8_3.9x4.9mm_P1.27mm;U13;somma x10 (2 per banda)
1;OPA1642AIDR;SOIC-8_3.9x4.9mm_P1.27mm;U14;servo DC (classe OPA2134 nel doc; OPA1642, SBOS484D)
1;OPA1654AIDR;SOIC-14_3.9x8.7mm_P1.27mm;U3;isolator lato L, sezioni 1-4
1;OPA1654AIDR;SOIC-14_3.9x8.7mm_P1.27mm;U4;isolator lato L, sezioni 5-8
1;OPA1654AIDR;SOIC-14_3.9x8.7mm_P1.27mm;U5;isolator lato L, sezioni 9-12
1;OPA1654AIDR;SOIC-14_3.9x8.7mm_P1.27mm;U6;isolator lato L, sezioni 13-16
1;OPA1654AIDR;SOIC-14_3.9x8.7mm_P1.27mm;U7;isolator lato L, sezioni 17-20
1;OPA1654AIDR;SOIC-14_3.9x8.7mm_P1.27mm;U8;isolator lato R, sezioni 1-4
1;OPA1654AIDR;SOIC-14_3.9x8.7mm_P1.27mm;U9;isolator lato R, sezioni 5-8
